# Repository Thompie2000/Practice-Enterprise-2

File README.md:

# Thomas Leemans

# Brievenbusmelder 
 
# Voor meer informatie over brievenbusmelder kan je vinden in een bestand info_brievenbusmelder

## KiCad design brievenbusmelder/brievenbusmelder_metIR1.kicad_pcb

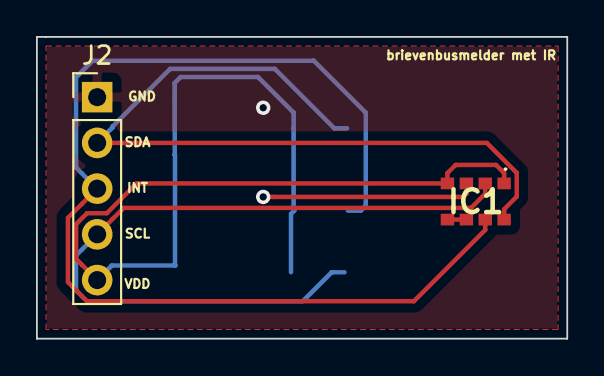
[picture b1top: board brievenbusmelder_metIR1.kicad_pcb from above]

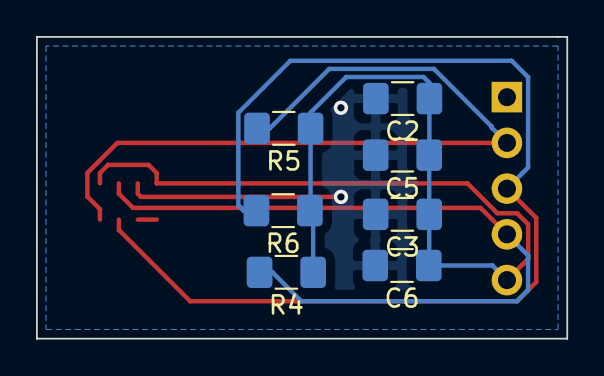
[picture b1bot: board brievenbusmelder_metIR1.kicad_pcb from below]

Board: 2 copper layers, 29.5 x 16.8 mm, 9 parts (7 on the bottom side), 6 nets.

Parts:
C2: 22µF; C_1206_3216Metric_Pad1.42x1.75mm_HandSolder
C3, C5: 100nF; C_1206_3216Metric_Pad1.42x1.75mm_HandSolder
C6: 10µF; C_1206_3216Metric_Pad1.42x1.75mm_HandSolder
IC1: VCNL3030X01-GS08; VCNL3030X01GS08
J2: Conn_01x05_Male; PinHeader_1x05_P2.54mm_Vertical
R4: 2.2k; R_1206_3216Metric_Pad1.42x1.75mm_HandSolder
R5: 2.2K; R_1206_3216Metric_Pad1.42x1.75mm_HandSolder
R6: 8.2K; R_1206_3216Metric_Pad1.42x1.75mm_HandSolder

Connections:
GND: C2.2, C3.2, C5.2, C6.2, IC1.3, J2.1
unnamed: C2.1, C3.1, C5.1, C6.1, IC1.1, IC1.4, J2.5, R4.1, R5.1, R6.1
unnamed: IC1.2, J2.4, R4.2
unnamed: IC1.5, IC1.6
unnamed: IC1.7, J2.3, R6.2
unnamed: IC1.8, J2.2, R5.2

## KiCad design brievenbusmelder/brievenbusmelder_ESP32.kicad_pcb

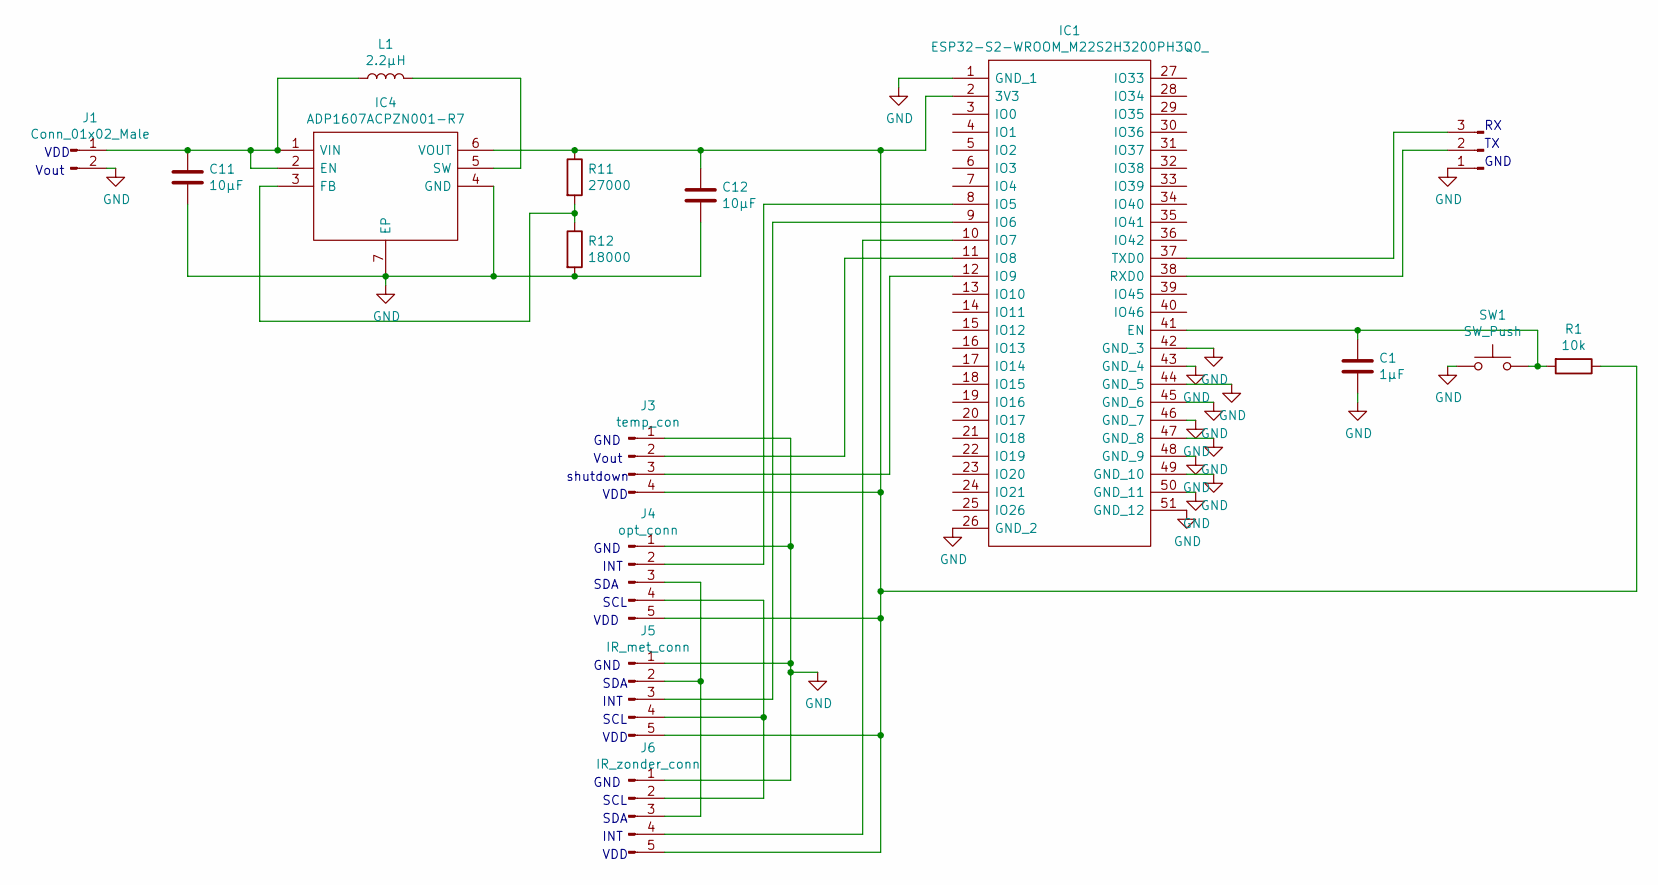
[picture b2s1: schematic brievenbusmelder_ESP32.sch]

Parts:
C1: 1µF; C_1206_3216Metric_Pad1.42x1.75mm_HandSolder
C11, C12: 10µF; C_1206_3216Metric_Pad1.42x1.75mm_HandSolder
IC1: ESP32-S2-WROOM_M22S2H3200PH3Q0_; ESP32S2WROOMM22S2H3200PH3Q0; Manufacturer_Part_Number ESP32-S2-WROOM(M22S2H3200PH3Q0); Mouser Part Number 356-ESP32S2WRM3200PH
IC4: ADP1607ACPZN001-R7; SON65P200X200X65-7N-D; Mouser Part Number 584-AP1607ACPZN001R7
J1: Conn_01x02_Male; PinHeader_1x02_P2.54mm_Vertical
J2: Conn_01x03_Male; PinHeader_1x03_P2.54mm_Vertical
J3: temp_con; PinHeader_1x04_P2.54mm_Vertical
J4: opt_conn; PinHeader_1x05_P2.54mm_Vertical
J5: IR_met_conn; PinHeader_1x05_P2.54mm_Vertical
J6: IR_zonder_conn; PinHeader_1x05_P2.54mm_Vertical
L1: 2.2µH; L_0805_2012Metric_Pad1.15x1.40mm_HandSolder
R1: 10k; R_1206_3216Metric_Pad1.42x1.75mm_HandSolder
R11: 27000; R_1206_3216Metric_Pad1.42x1.75mm_HandSolder
R12: 18000; R_1206_3216Metric_Pad1.42x1.75mm_HandSolder
SW1: SW_Push; Drukknop_OFF_(ON)

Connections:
GND: C1.2, C11.2, C12.2, IC1.1 (GND_1), IC1.26 (GND_2), IC1.42 (GND_3), IC1.43 (GND_4), IC1.44 (GND_5), IC1.45 (GND_6), IC1.46 (GND_7), IC1.47 (GND_8), IC1.48 (GND_9), IC1.49 (GND_10), IC1.50 (GND_11), IC1.51 (GND_12), IC4.4 (GND), IC4.7 (EP), J1.2, J2.1, J3.1, J4.1, J5.1, J6.1, R12.2, SW1.1
unnamed: C1.1, IC1.41 (EN), R1.2, SW1.3 (2)
unnamed: C11.1, IC4.1 (VIN), IC4.2 (EN), J1.1, L1.1
unnamed: C12.1, IC1.2 (3V3), IC4.6 (VOUT), J3.4, J4.5, J5.5, J6.5, R1.1, R11.1
unnamed: IC1.8 (IO5), J4.2
unnamed: IC1.9 (IO6), J5.3
unnamed: IC1.10 (IO7), J6.4
unnamed: IC1.11 (IO8), J3.2
unnamed: IC1.12 (IO9), J3.3
unnamed: IC1.37 (TXD0), J2.3
unnamed: IC1.38 (RXD0), J2.2
unnamed: IC4.3 (FB), R11.2, R12.1
unnamed: IC4.5 (SW), L1.2
unnamed: J4.3, J5.2, J6.3
unnamed: J4.4, J5.4, J6.2

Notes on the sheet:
VDD
Vout
GND
GND
shutdown
INT
SDA
SCL

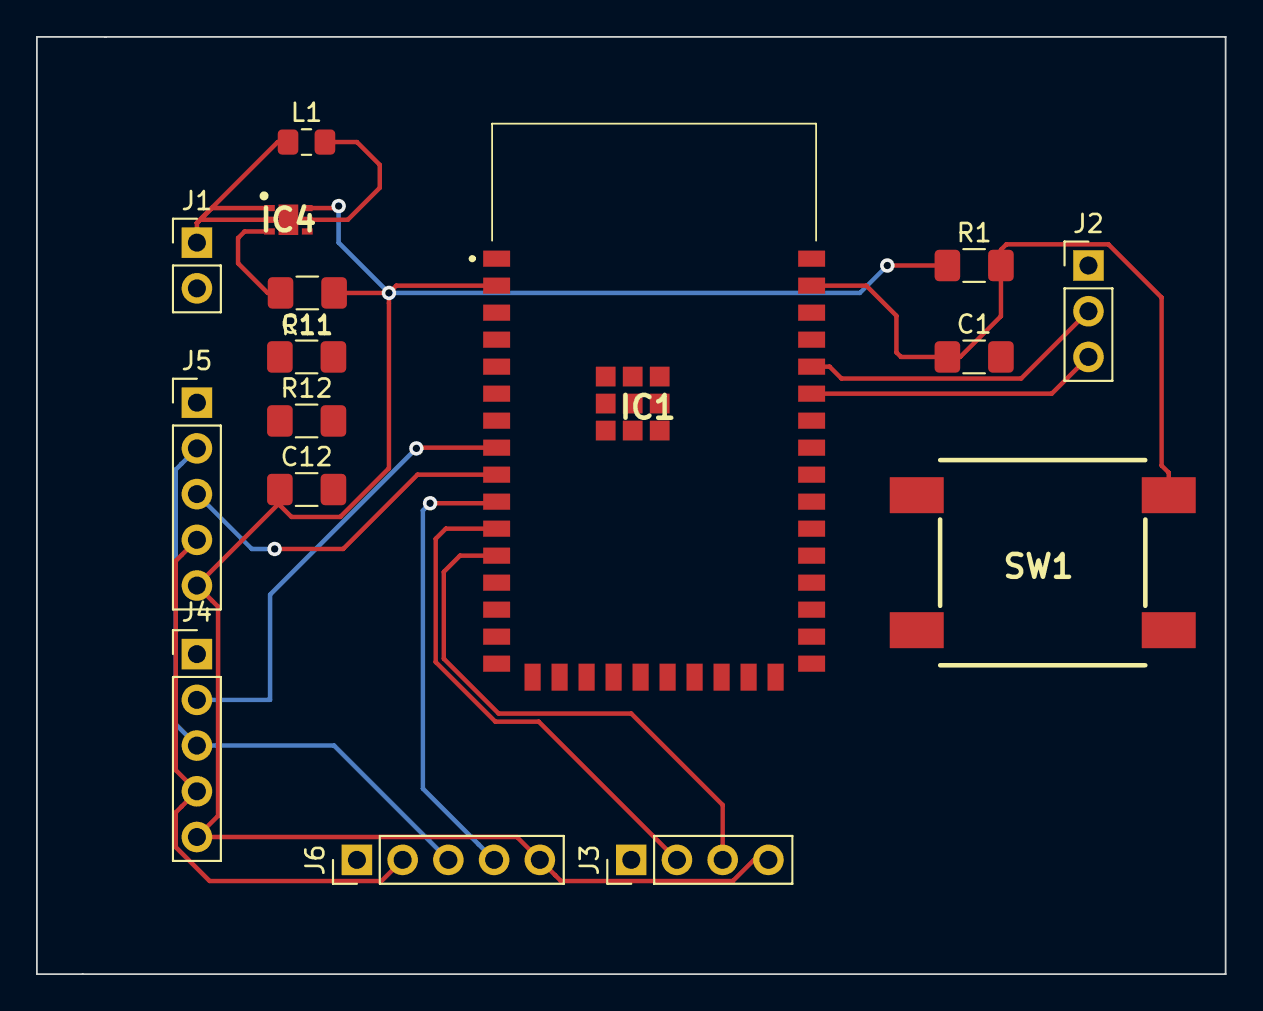
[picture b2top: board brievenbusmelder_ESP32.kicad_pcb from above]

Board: 2 copper layers, 66.0 x 52.1 mm, 16 parts (0 on the bottom side), 15 nets.

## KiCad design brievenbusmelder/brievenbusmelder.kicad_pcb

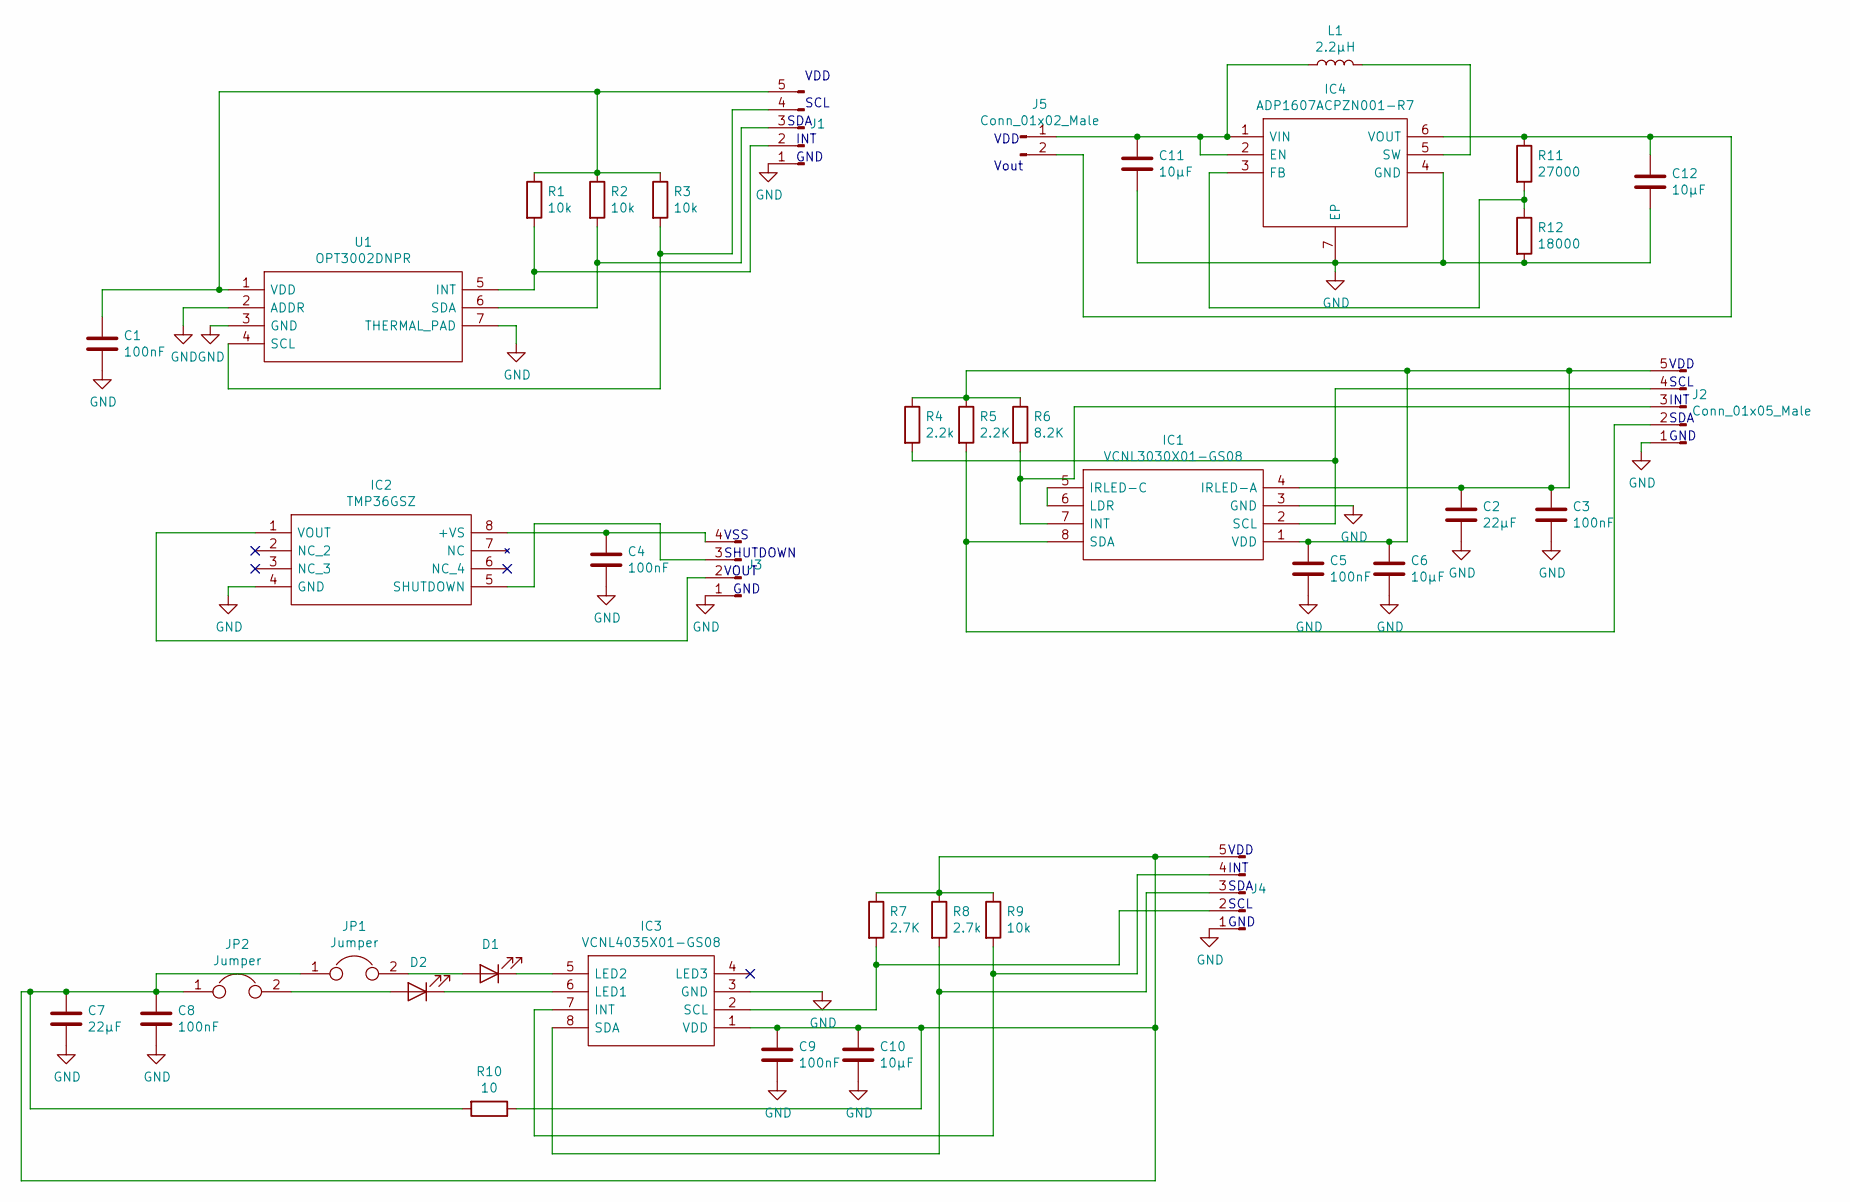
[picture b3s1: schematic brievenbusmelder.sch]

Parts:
C1, C3, C4, C5, C8, C9: 100nF; C_1206_3216Metric_Pad1.42x1.75mm_HandSolder
C2, C7: 22µF; C_1206_3216Metric_Pad1.42x1.75mm_HandSolder
C6, C10, C11, C12: 10µF; C_1206_3216Metric_Pad1.42x1.75mm_HandSolder
D1: IR; LED_1206_3216Metric_Pad1.42x1.75mm_HandSolder
D2: IR; OP294
IC1: VCNL3030X01-GS08; VCNL3030X01GS08; Manufacturer_Part_Number VCNL3030X01-GS08; Mouser Part Number 78-VCNL3030X01-GS08
IC2: TMP36GSZ; SOIC127P600X175-8N; Mouser Part Number 584-TMP36GSZ
IC3: VCNL4035X01-GS08; naderingssensor_zonderIR; Mouser Part Number 78-VCNL4035X01-GS08
IC4: ADP1607ACPZN001-R7; SON65P200X200X65-7N-D; Mouser Part Number 584-AP1607ACPZN001R7
J1, J2, J4: Conn_01x05_Male; PinHeader_1x05_P2.54mm_Vertical
J3: Conn_01x04_Male; PinHeader_1x04_P2.54mm_Vertical
J5: Conn_01x02_Male; PinHeader_1x02_P2.54mm_Vertical
JP1, JP2: Jumper; PinHeader_1x02_P2.54mm_Vertical
L1: 2.2µH; L_0805_2012Metric_Pad1.15x1.40mm_HandSolder
R1, R2, R3, R9: 10k; R_1206_3216Metric_Pad1.42x1.75mm_HandSolder
R4: 2.2k; R_1206_3216Metric_Pad1.42x1.75mm_HandSolder
R5: 2.2K; R_1206_3216Metric_Pad1.42x1.75mm_HandSolder
R6: 8.2K; R_1206_3216Metric_Pad1.42x1.75mm_HandSolder
R7: 2.7K; R_1206_3216Metric_Pad1.42x1.75mm_HandSolder
R8: 2.7k; R_1206_3216Metric_Pad1.42x1.75mm_HandSolder
R10: 10; R_1206_3216Metric_Pad1.42x1.75mm_HandSolder
R11: 27000; R_1206_3216Metric_Pad1.42x1.75mm_HandSolder
R12: 18000; R_1206_3216Metric_Pad1.42x1.75mm_HandSolder
U1: OPT3002DNPR; Mouser Part Number 595-OPT3002DNPR

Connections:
GND: C1.2, C2.2, C3.2, C4.2, C5.2, C6.2, C7.2, C8.2, C9.2, C10.2, C11.2, C12.2, IC1.3 (GND), IC2.4 (GND), IC3.3 (GND), IC4.4 (GND), IC4.7 (EP), J1.1, J2.1, J3.1, J4.1, R12.2, U1.2 (ADDR), U1.3 (GND), U1.7 (THERMAL_PAD)
unnamed: C1.1, J1.5, R1.1, R2.1, R3.1, U1.1 (VDD)
unnamed: C2.1, C3.1, C5.1, C6.1, IC1.1 (VDD), IC1.4 (IRLED-A), J2.5, R4.1, R5.1, R6.1
unnamed: C4.1, IC2.8 (+VS), J3.4
unnamed: C7.1, C8.1, C9.1, C10.1, IC3.1 (VDD), J4.5, JP1.1, JP2.1, R7.1, R8.1, R9.1, R10.1, R10.2
unnamed: C11.1, IC4.1 (VIN), IC4.2 (EN), J5.1, L1.1
unnamed: C12.1, IC4.6 (VOUT), J5.2, R11.1
unnamed: D1.1 (K), IC3.5 (LED2)
unnamed: D1.2 (A), JP1.2
unnamed: D2.1 (K), IC3.6 (LED1)
unnamed: D2.2 (A), JP2.2
unnamed: IC1.2 (SCL), J2.4, R4.2
unnamed: IC1.5 (IRLED-C), IC1.6 (LDR)
unnamed: IC1.7 (INT), J2.3, R6.2
unnamed: IC1.8 (SDA), J2.2, R5.2
unnamed: IC2.1 (VOUT), J3.2
unnamed: IC2.5 (SHUTDOWN~), J3.3
unnamed: IC3.2 (SCL), J4.2, R7.2
unnamed: IC3.7 (INT), J4.4, R9.2
unnamed: IC3.8 (SDA), J4.3, R8.2
unnamed: IC4.3 (FB), R11.2, R12.1
unnamed: IC4.5 (SW), L1.2
unnamed: J1.2, R1.2, U1.5 (INT)
unnamed: J1.3, R2.2, U1.6 (SDA)
unnamed: J1.4, R3.2, U1.4 (SCL)

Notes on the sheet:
VDD
SCL
SDA
INT
GND
GND
VOUT
SHUTDOWN
VSS
Vout

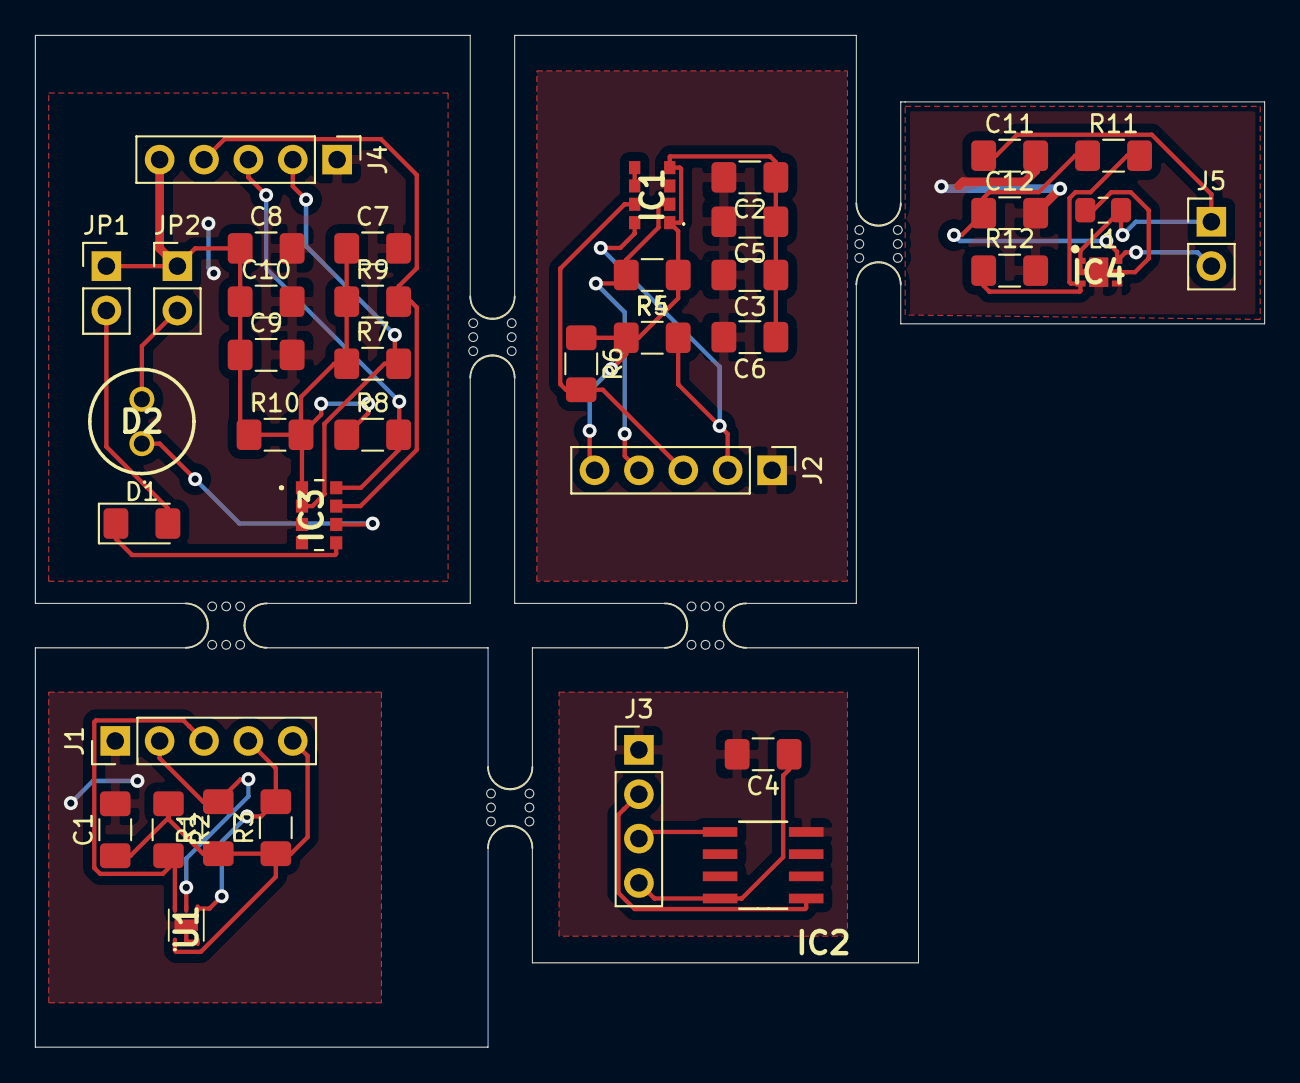
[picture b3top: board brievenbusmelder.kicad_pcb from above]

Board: 2 copper layers, 70.4 x 57.9 mm, 44 parts (0 on the bottom side), 25 nets.

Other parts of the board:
mouse-bite-2.54mm-slot, mouse-bite-2.54mm-slot#2, mouse-bite-2.54mm-slot#3, mouse-bite-2.54mm-slot#4, mouse-bite-2.54mm-slot#5: VAL**; mouse-bite-2.54mm-slot

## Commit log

2021-03-06 Kicad
2021-03-06 info
2021-04-18 Update brievenbusmelder_metIR.kicad_pcb-bak
2021-04-18 Create brievenbusmelder_metIR.sch-bak
2021-04-18 Update brievenbusmelder_zonderIR.sch-bak
2021-04-18 Update fp-info-cache
